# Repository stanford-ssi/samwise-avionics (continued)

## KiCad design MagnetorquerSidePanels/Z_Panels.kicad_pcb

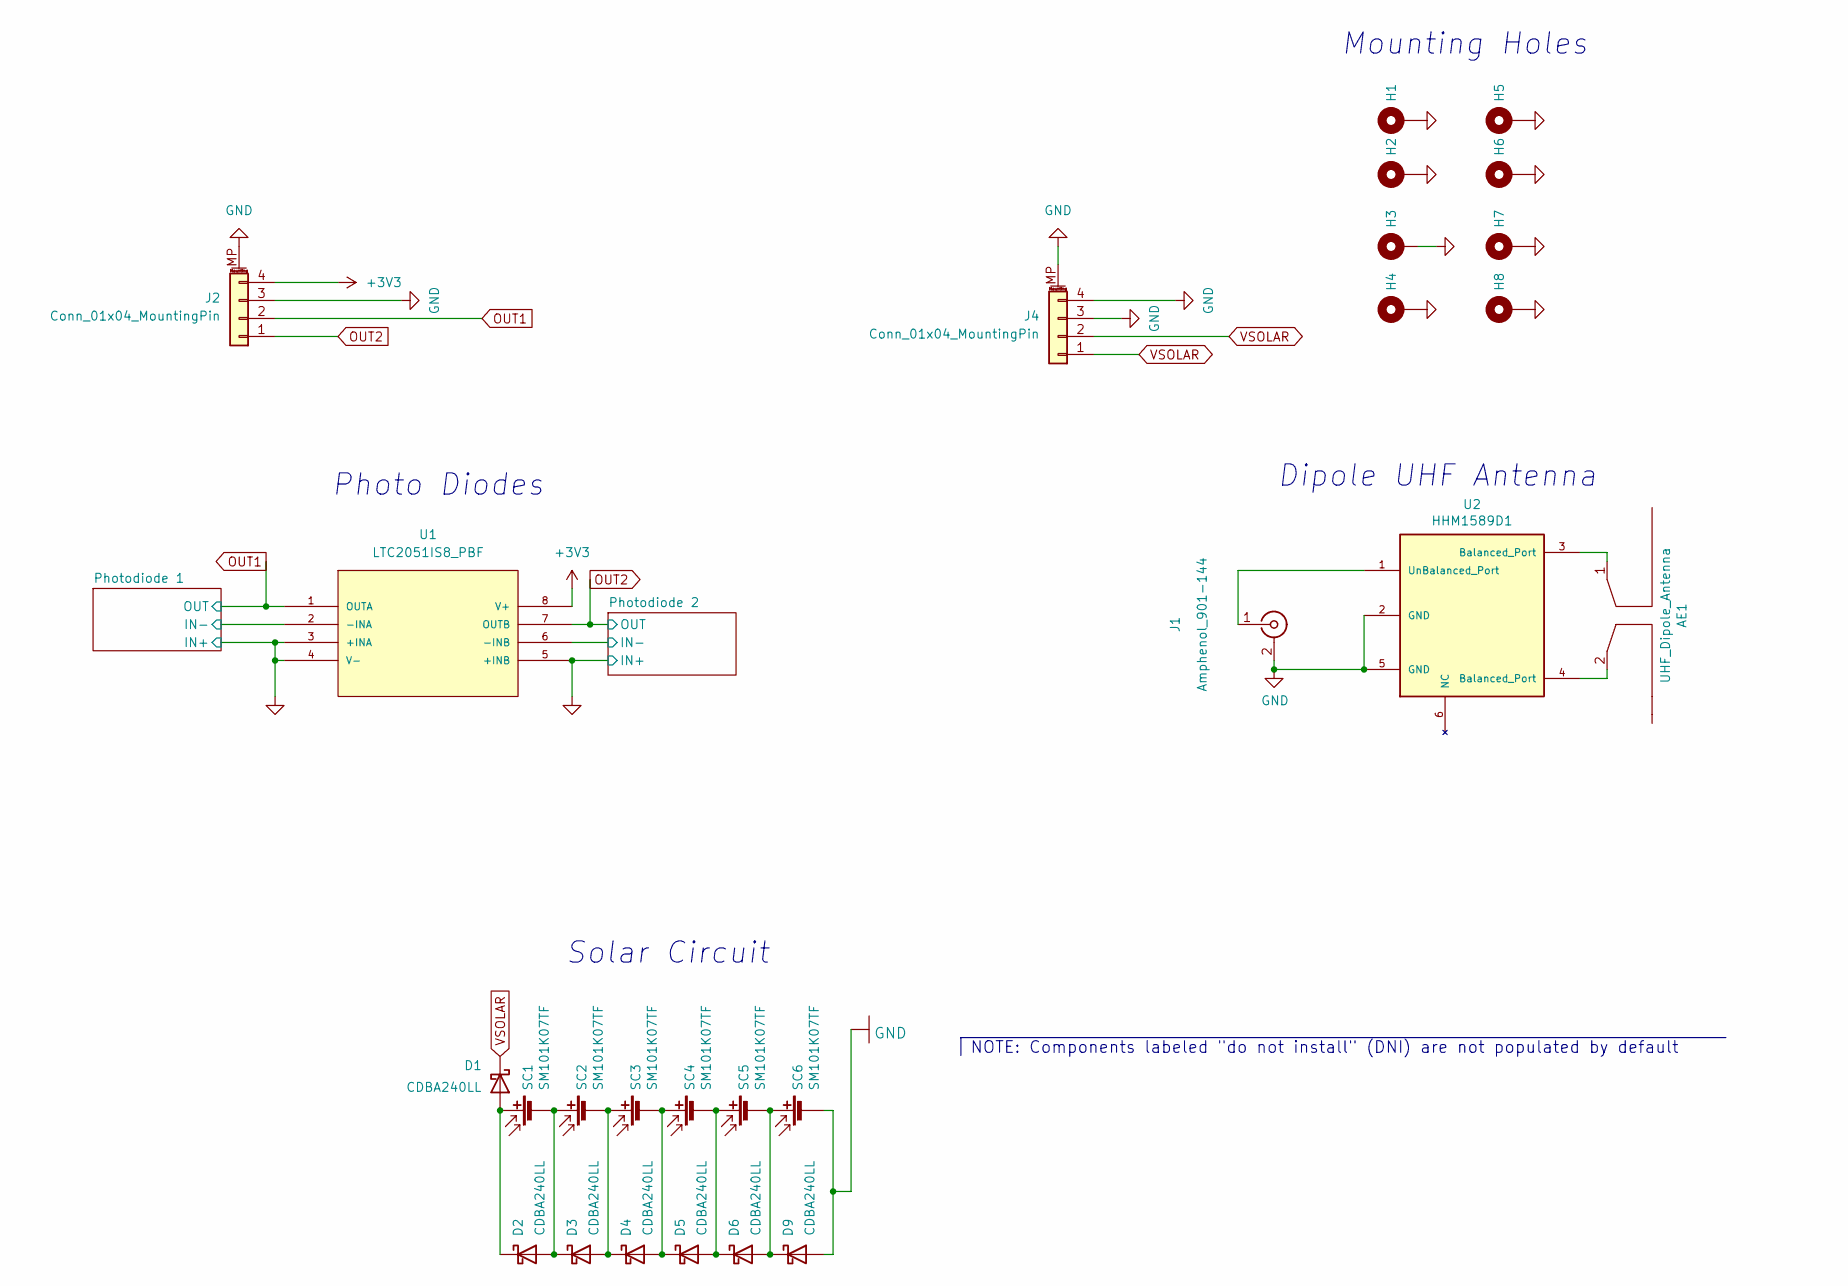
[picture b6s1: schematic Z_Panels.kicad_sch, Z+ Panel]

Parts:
AE1: UHF_Dipole_Antenna; UHF_Dipole_Antenna_Mount
D1, D2, D3, D4, D5, D6, D9: CDBA240LL; DO-214AC
H1, H2, H3, H4, H5, H6, H7, H8: MountingHole_2.2mm_M2_DIN965_Pad_TopBottom
J1: Amphenol_901-144; SMA_Amphenol_901-144_Vertical
J2, J4: Conn_01x04_MountingPin; CON_2053380004
SC1, SC2, SC3, SC4, SC5, SC6: SM101K07TF
U1: LTC2051IS8_PBF; LTC2051HS8#PBF; MANUFACTURER_PART_NUMBER ltc2051is8
U2: HHM1589D1

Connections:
+3V3: J2.4, U1.8 (V+)
/Photodiode 1/IN-: U1.2 (-INA); also elsewhere on the board
GND: D9.2 (A), H1.1, H2.1, H3.1, H4.1, H5.1, H6.1, H7.1, H8.1, J1.2 (Ext), J2.3, J2.MP (MountPin), J4.3, J4.4, J4.MP (MountPin), SC6.2 (-), U1.3 (+INA), U1.4 (V-), U1.5 (+INB), U2.2 (GND), U2.5 (GND); also elsewhere on the board
unnamed: AE1.1, U2.3 (Balanced_Port)
unnamed: AE1.2, U2.4 (Balanced_Port)
unnamed: D1.2 (A), D2.1 (K), SC1.1 (+)
unnamed: D2.2 (A), D3.1 (K), SC1.2 (-), SC2.1 (+)
unnamed: D3.2 (A), D4.1 (K), SC2.2 (-), SC3.1 (+)
unnamed: D4.2 (A), D5.1 (K), SC3.2 (-), SC4.1 (+)
unnamed: D5.2 (A), D6.1 (K), SC4.2 (-), SC5.1 (+)
unnamed: J1.1 (In), U2.1 (UnBalanced_Port)
OUT1: J2.2, U1.1 (OUTA); also elsewhere on the board
OUT2: J2.1, U1.7 (OUTB); also elsewhere on the board
VSOLAR: D1.1 (K), J4.1, J4.2

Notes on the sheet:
NOTE: Components labeled "do not install" (DNI) are not populated by default
Solar Circuit
Photo Diodes
Dipole UHF Antenna
Mounting Holes

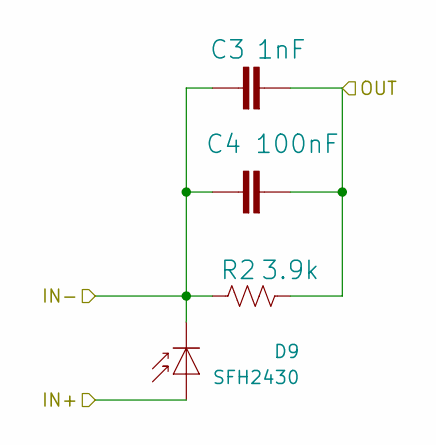
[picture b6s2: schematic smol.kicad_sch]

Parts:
C3: 1nF; C_0603_1608Metric
C4: 100nF; C_0603_1608Metric
D9: SFH2430; Osram_SFH2430
R2: 3.9k; R_0603_1608Metric

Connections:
GND: D9.2 (A); also elsewhere on the board
OUT2: C3.2, C4.2, R2.2; also elsewhere on the board

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
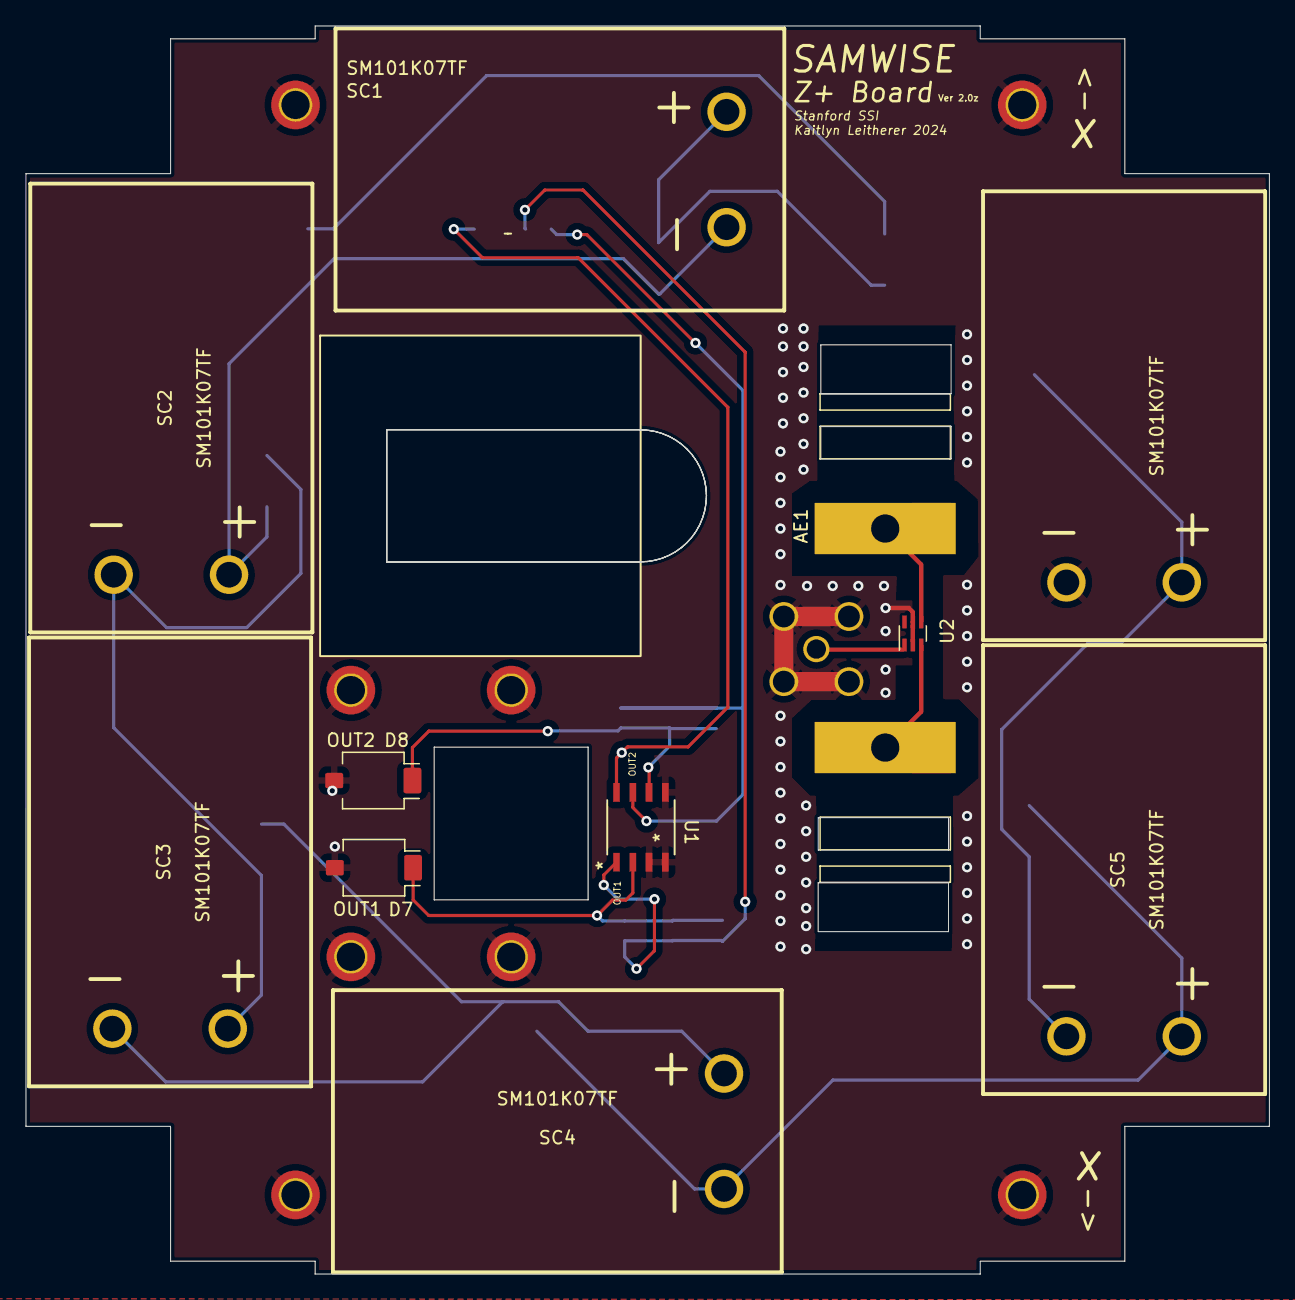
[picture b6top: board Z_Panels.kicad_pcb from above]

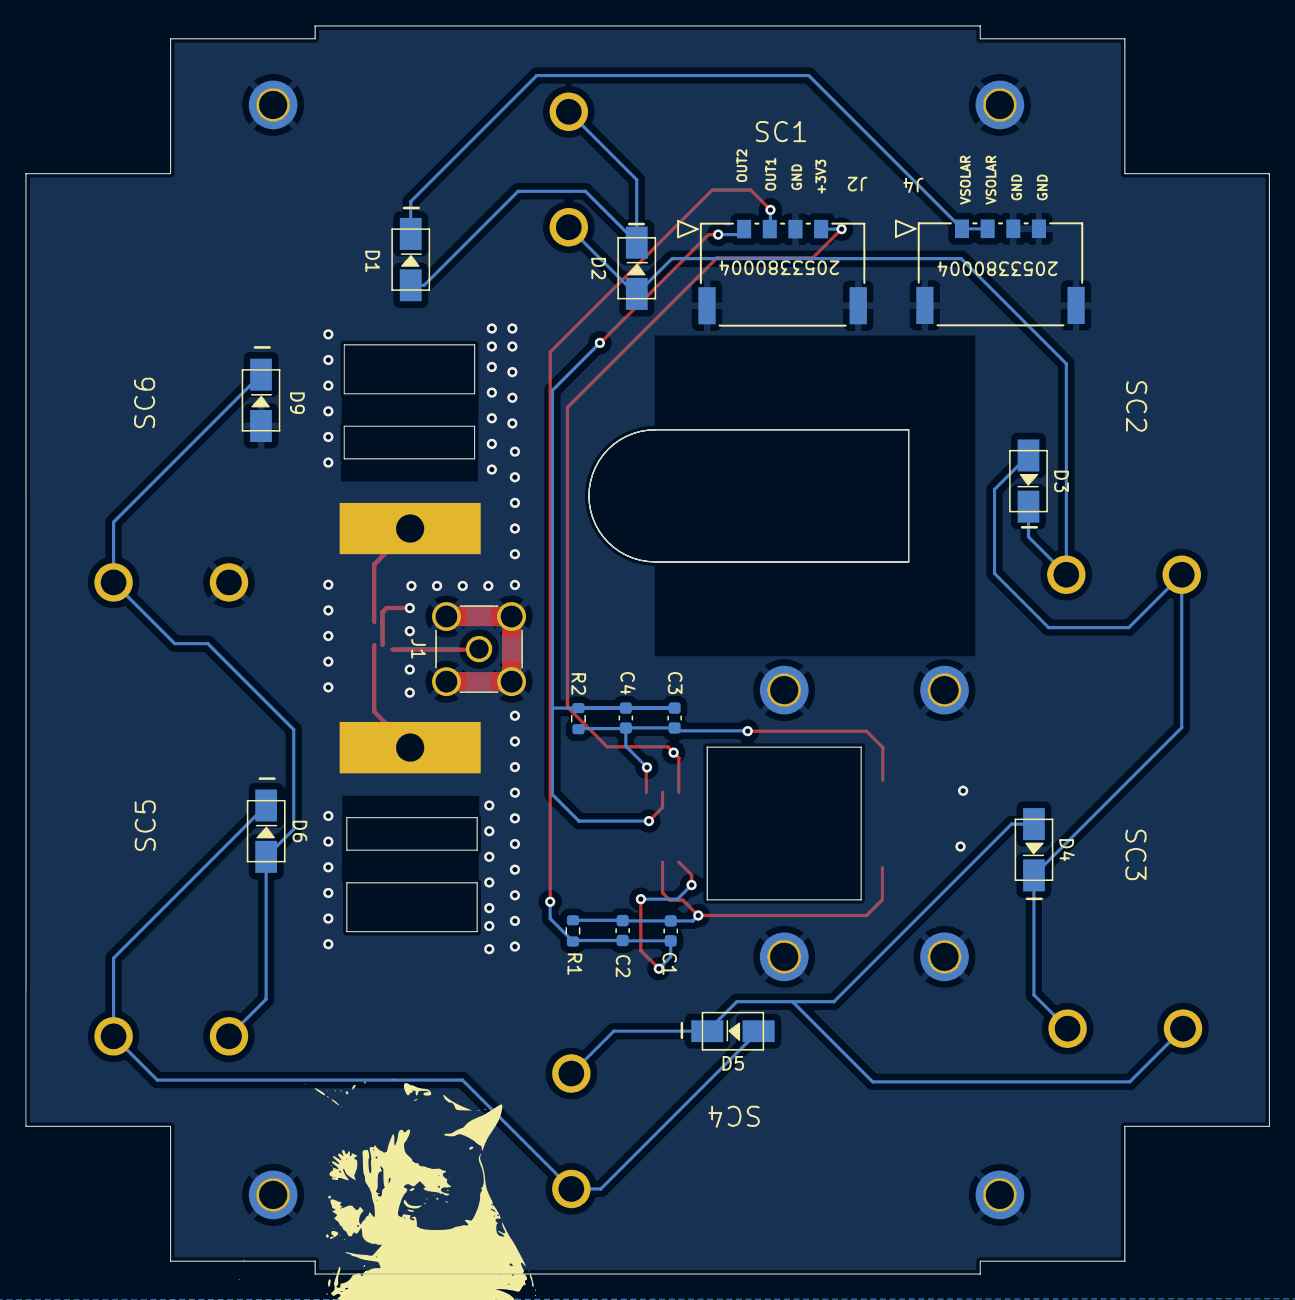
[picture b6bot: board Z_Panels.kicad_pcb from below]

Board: 4 copper layers, 97.0 x 97.3 mm, 36 parts (16 on the bottom side), 16 nets.

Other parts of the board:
AE2: WPC.25A
C1: 1nF; C_0603_1608Metric
C2: 0.1uF; C_0603_1608Metric
D7, D8: SFH2430; Osram_SFH2430
R1: 3.9k; R_0603_1608Metric

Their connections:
/Photodiode 1/IN-: C1.1, C2.1, D7.1 (K), R1.1; also elsewhere on the board
GND: D7.2 (A), D8.2 (A); also elsewhere on the board
OUT1: C1.2, C2.2, R1.2; also elsewhere on the board

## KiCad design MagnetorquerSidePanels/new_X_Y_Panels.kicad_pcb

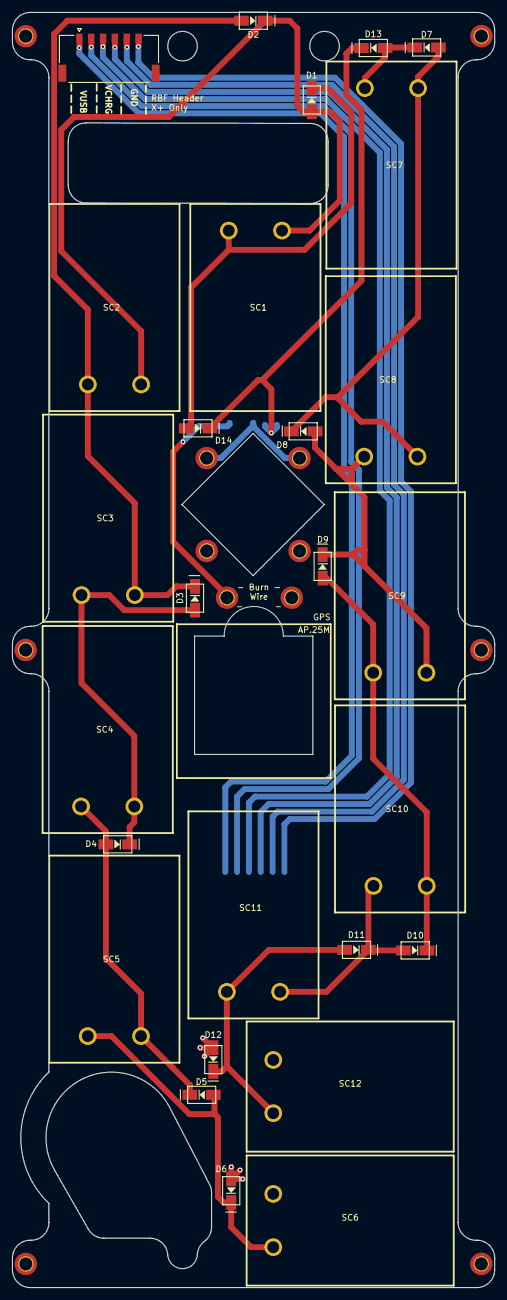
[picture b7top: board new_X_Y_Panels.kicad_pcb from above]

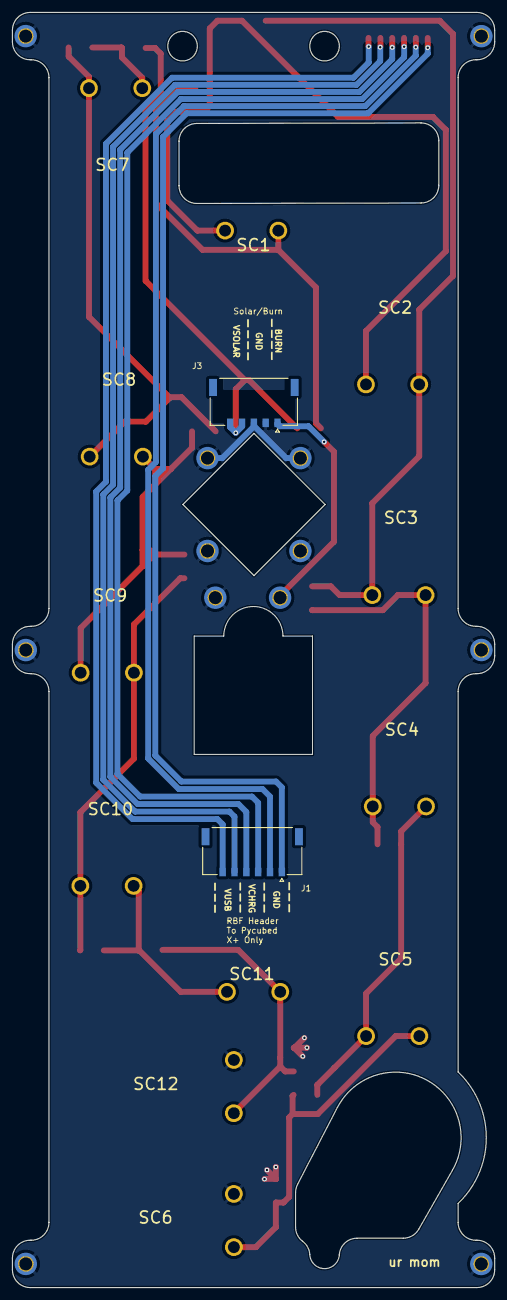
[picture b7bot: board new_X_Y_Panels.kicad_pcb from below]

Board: 2 copper layers, 81.5 x 215.5 mm, 42 parts (2 on the bottom side), 21 nets.

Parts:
AE1: AP.25M
D1, D2, D3, D4, D5, D6, D7, D8, D9, D10, D11, D12, D13, D14: CDBA240LL; DO-214AC
H1, H2, H3, H4, H5, H6, H7, H8, H9, H10, H11, H12: MountingHole_Pad; MountingHole_2.2mm_M2_DIN965_Pad_TopBottom
J1, J2: 2053380006; MOLEX_2053380006
J3: 2053380005; MOLEX_2053380005
SC1, SC2, SC3, SC4, SC5, SC6, SC7, SC8, SC9, SC10, SC11, SC12: SM101K07TF

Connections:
/PYCUBED_GND: J1.5, J2.5
/PYCUBED_GNDREF: J1.6, J2.6
/VBATT: J1.4, J2.4
/VCHRG: J1.3, J2.3
/VUSB_BATT: J1.2, J2.2
/VUSB_OUT: J1.1, J2.1
BURN: H1.1, J3.1
GND: D6.2 (A), D12.2 (A), H2.1, H3.1, H4.1, H5.1, H6.1, H7.1, H8.1, H9.1, H10.1, H11.1, H12.1, J3.2, J3.3, SC6.2 (-), SC12.2 (-)
unnamed: D1.2 (A), D2.1 (K), SC1.2 (-), SC2.1 (+)
unnamed: D1.1 (K), D14.2 (A), SC1.1 (+)
unnamed: D2.2 (A), D3.1 (K), SC2.2 (-), SC3.1 (+)
unnamed: D3.2 (A), D4.1 (K), SC3.2 (-), SC4.1 (+)
unnamed: D4.2 (A), D5.1 (K), SC4.2 (-), SC5.1 (+)
unnamed: D5.2 (A), D6.1 (K), SC5.2 (-), SC6.1 (+)
unnamed: D7.2 (A), D8.1 (K), SC7.2 (-), SC8.1 (+)
unnamed: D8.2 (A), D9.1 (K), SC8.2 (-), SC9.1 (+)
unnamed: D10.2 (A), D11.1 (K), SC10.2 (-), SC11.1 (+)
unnamed: D9.2 (A), D10.1 (K), SC9.2 (-), SC10.1 (+)
unnamed: D11.2 (A), D12.1 (K), SC11.2 (-), SC12.1 (+)
unnamed: D7.1 (K), D13.2 (A), SC7.1 (+)
VSOLAR: D13.1 (K), D14.1 (K), J3.4, J3.5
